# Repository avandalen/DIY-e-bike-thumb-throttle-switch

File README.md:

# DIY-e-bike-thumb-throttle-switch
For the speed control of my Maxun One solar bike, I use an up-down thumb-throttle switch. Normally, such a throttle is mounted between grip and the brake lever which increases the distance between them. That's why I made a throttle that is mounted on top of the brake lever clamp so that no extra space is needed on the handlebar.
See the full article here:
https://www.avdweb.nl/solar-bike/mechanical-issues/diy-ergonomic-space-saving-e-bike-thumb-throttle-switch

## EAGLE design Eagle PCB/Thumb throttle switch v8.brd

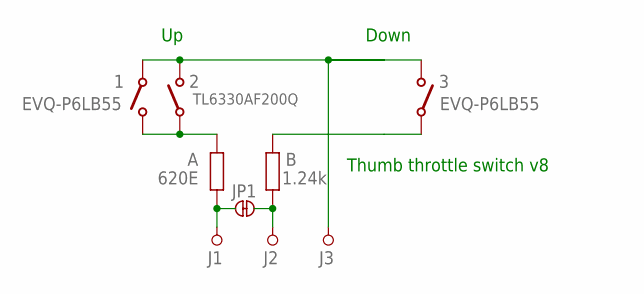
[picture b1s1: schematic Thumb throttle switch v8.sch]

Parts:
1, 3: EVQ-P6LB55; TACTILE_SWITCH_SMD-2
2: TL6330AF200Q; TACTILE_SWITCH_SMD_4.6X2.8MM
A: 620E; 0603
B: 1.24k; 0603
J1, J2, J3: nc; PIN-0.3MM
JP1: nc; JUMPER_NC

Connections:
J1: A.1, J1.1, JP1.1, JP1.1A (1)
J2: B.1, J2.1, JP1.2, JP1.2B (2)
J3: 1.2, 2.1 (O), 2.4 (O), 3.1 (O), J3.1
unnamed: 1.1 (O), 2.2, 2.3, A.2
unnamed: 3.2, B.2

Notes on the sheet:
Down
Thumb throttle switch v8

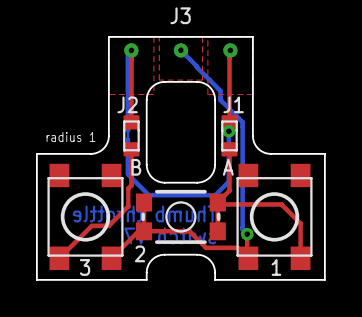
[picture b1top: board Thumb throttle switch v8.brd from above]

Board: 2 copper layers, 16.0 x 13.5 mm, 9 parts (1 on the bottom side), 5 nets.

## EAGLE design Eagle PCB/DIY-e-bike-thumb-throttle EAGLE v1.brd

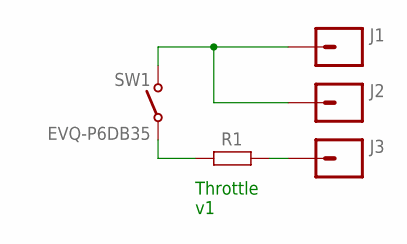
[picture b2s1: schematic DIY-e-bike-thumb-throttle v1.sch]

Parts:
J1, J2, J3: M01SMD-4.5X1.5; PAD-1.5X4.5
R1: SMD-R-0603-SMALL; 0603-SMALL
SW1: EVQ-P6DB35; TACTILE_SWITCH_SMD-2

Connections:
unnamed: J3.P$1, R1.2
unnamed: R1.1, SW1.2, SW1.3
unnamed: J1.P$1, J2.P$1, SW1.1 (O), SW1.4 (O)

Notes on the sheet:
Throttle v1

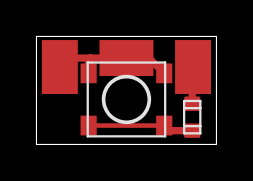
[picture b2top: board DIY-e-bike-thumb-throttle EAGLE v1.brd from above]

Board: 2 copper layers, 10.0 x 6.0 mm, 5 parts (0 on the bottom side), 3 nets.

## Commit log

2021-11-17 Create c
2023-10-03 Create Freecad
2023-10-03 Create g

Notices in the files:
parts and their libraries:
SparkFun-Connectors: Licensing: Creative Commons ShareAlike 4.0 International - https://creativecommons.org/licenses/by-sa/4.0
